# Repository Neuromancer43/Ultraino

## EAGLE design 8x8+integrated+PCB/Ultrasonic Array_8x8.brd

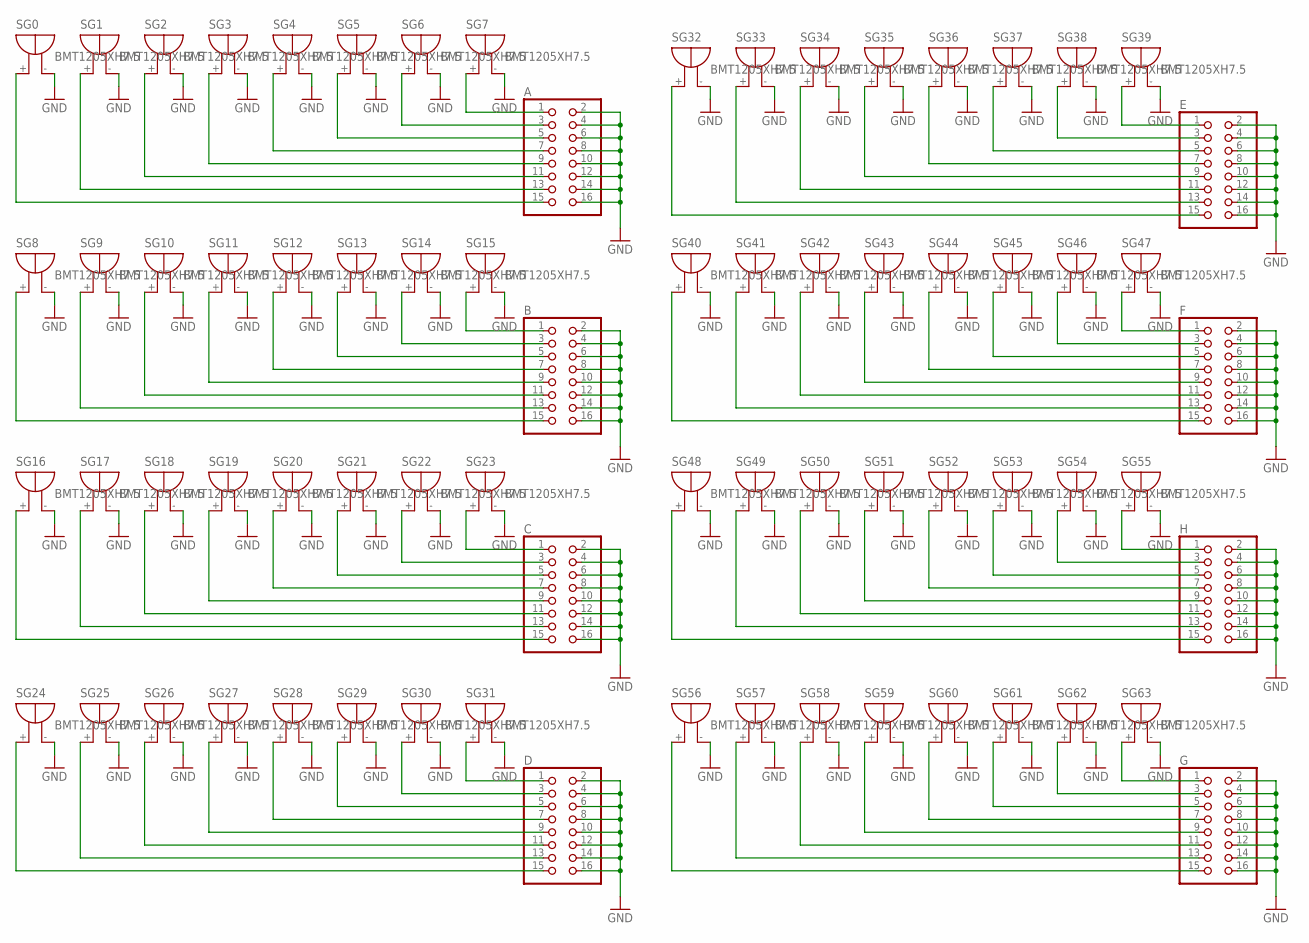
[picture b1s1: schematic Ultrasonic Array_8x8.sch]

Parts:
A: PINHD-2X8; 2X08
B: PINHD-2X8; 2X08
C: PINHD-2X8; 2X08
D: PINHD-2X8; 2X08
E: PINHD-2X8; 2X08
F: PINHD-2X8; 2X08
G: PINHD-2X8; 2X08
H: PINHD-2X8; 2X08
SG0, SG1, SG2, SG3, SG4, SG5, SG6, SG7, SG8, SG9, SG10, SG11, SG12, SG13, SG14, SG15, SG16, SG17, SG18, SG19, SG20, SG21, SG22, SG23, SG24, SG25, SG26, SG27, SG28, SG29, SG30, SG31, SG32, SG33, SG34, SG35, SG36, SG37, SG38, SG39, SG40, SG41, SG42, SG43, SG44, SG45, SG46, SG47, SG48, SG49, SG50, SG51, SG52, SG53, SG54, SG55, SG56, SG57, SG58, SG59, SG60, SG61, SG62, SG63: BMT1205XH7.5

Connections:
GND: A.2, A.4, A.6, A.8, A.10, A.12, A.14, A.16, B.2, B.4, B.6, B.8, B.10, B.12, B.14, B.16, C.2, C.4, C.6, C.8, C.10, C.12, C.14, C.16, D.2, D.4, D.6, D.8, D.10, D.12, D.14, D.16, E.2, E.4, E.6, E.8, E.10, E.12, E.14, E.16, F.2, F.4, F.6, F.8, F.10, F.12, F.14, F.16, G.2, G.4, G.6, G.8, G.10, G.12, G.14, G.16, H.2, H.4, H.6, H.8, H.10, H.12, H.14, H.16, SG0.-, SG1.-, SG2.-, SG3.-, SG4.-, SG5.-, SG6.-, SG7.-, SG8.-, SG9.-, SG10.-, SG11.-, SG12.-, SG13.-, SG14.-, SG15.-, SG16.-, SG17.-, SG18.-, SG19.-, SG20.-, SG21.-, SG22.-, SG23.-, SG24.-, SG25.-, SG26.-, SG27.-, SG28.-, SG29.-, SG30.-, SG31.-, SG32.-, SG33.-, SG34.-, SG35.-, SG36.-, SG37.-, SG38.-, SG39.-, SG40.-, SG41.-, SG42.-, SG43.-, SG44.-, SG45.-, SG46.-, SG47.-, SG48.-, SG49.-, SG50.-, SG51.-, SG52.-, SG53.-, SG54.-, SG55.-, SG56.-, SG57.-, SG58.-, SG59.-, SG60.-, SG61.-, SG62.-, SG63.-
unnamed: A.1, SG7.+
unnamed: A.3, SG6.+
unnamed: A.5, SG5.+
unnamed: A.7, SG4.+
unnamed: A.9, SG3.+
unnamed: A.11, SG2.+
unnamed: A.13, SG1.+
unnamed: A.15, SG0.+
unnamed: B.1, SG15.+
unnamed: B.3, SG14.+
unnamed: B.5, SG13.+
unnamed: B.7, SG12.+
unnamed: B.9, SG11.+
unnamed: B.11, SG10.+
unnamed: B.13, SG9.+
unnamed: B.15, SG8.+
unnamed: C.1, SG23.+
unnamed: C.3, SG22.+
unnamed: C.5, SG21.+
unnamed: C.7, SG20.+
unnamed: C.9, SG19.+
unnamed: C.11, SG18.+
unnamed: C.13, SG17.+
unnamed: C.15, SG16.+
unnamed: D.1, SG31.+
unnamed: D.3, SG30.+
unnamed: D.5, SG29.+
unnamed: D.7, SG28.+
unnamed: D.9, SG27.+
unnamed: D.11, SG26.+
unnamed: D.13, SG25.+
unnamed: D.15, SG24.+
unnamed: E.1, SG39.+
unnamed: E.3, SG38.+
unnamed: E.5, SG37.+
unnamed: E.7, SG36.+
unnamed: E.9, SG35.+
unnamed: E.11, SG34.+
unnamed: E.13, SG33.+
unnamed: E.15, SG32.+
unnamed: F.1, SG47.+
unnamed: F.3, SG46.+
unnamed: F.5, SG45.+
unnamed: F.7, SG44.+
unnamed: F.9, SG43.+
unnamed: F.11, SG42.+
unnamed: F.13, SG41.+
unnamed: F.15, SG40.+
unnamed: H.1, SG55.+
unnamed: H.3, SG54.+
unnamed: H.5, SG53.+
unnamed: H.7, SG52.+
unnamed: H.9, SG51.+
unnamed: H.11, SG50.+
unnamed: H.13, SG49.+
unnamed: H.15, SG48.+
unnamed: G.1, SG63.+
unnamed: G.3, SG62.+
unnamed: G.5, SG61.+
unnamed: G.7, SG60.+
unnamed: G.9, SG59.+
unnamed: G.11, SG58.+
unnamed: G.13, SG57.+
unnamed: G.15, SG56.+

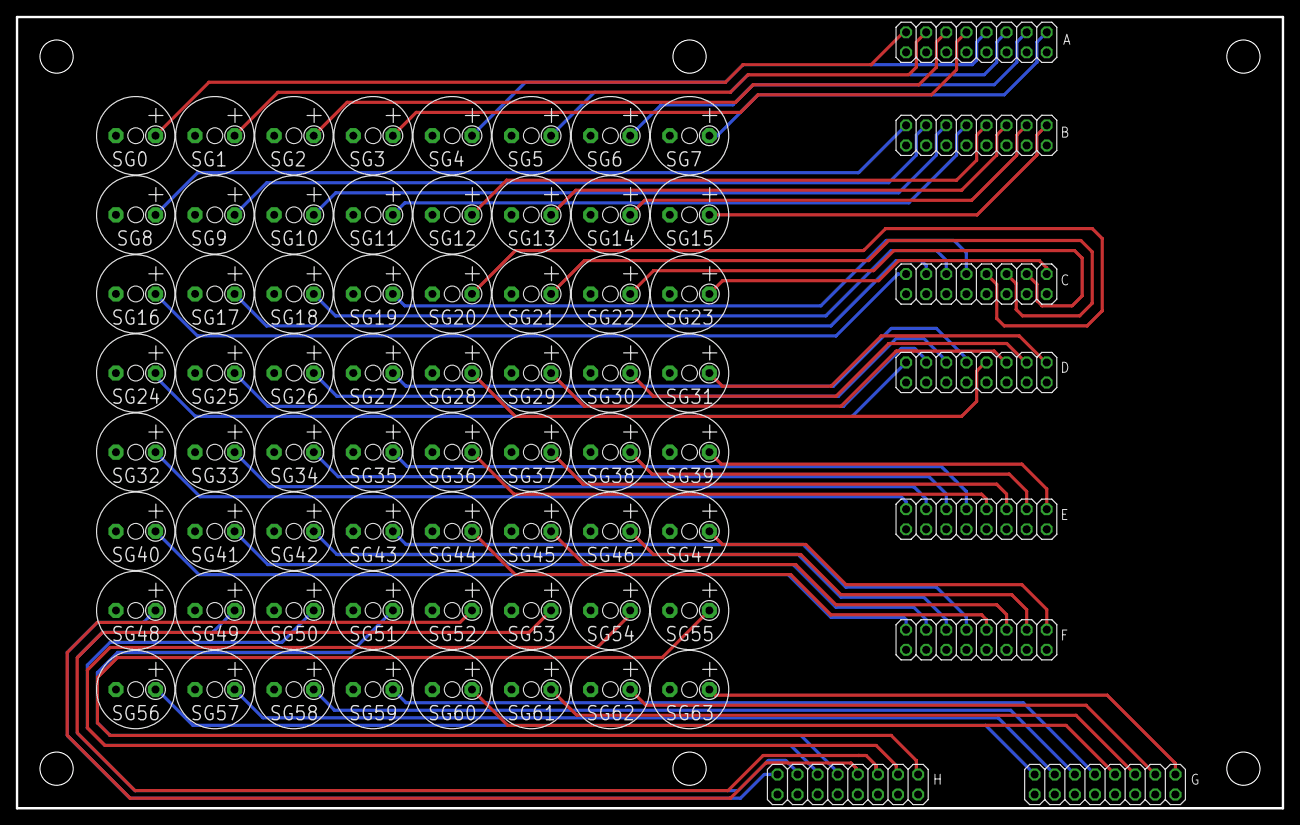
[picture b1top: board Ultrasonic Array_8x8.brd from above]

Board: 2 copper layers, 160.0 x 100.0 mm, 72 parts (0 on the bottom side), 65 nets.

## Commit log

2018-10-01 build project
2019-06-04 Zhuoyue Cup
